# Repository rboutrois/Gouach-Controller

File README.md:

# Gouach controller

## Peripherals pinout
### Throttle
- +5V
- ADC_THROTTLE
- GND

### Torque sensor
- +5V
- PFS
- ADC_TORQUE
- CRUISE
- GND

### Brake
- +5V
- IO_BRAKE
- ADC_BRAKE
- GND

### Motor
3 Phases
- +5V
- HALL_1
- HALL_2
- HALL_3
- TEMPERATURE
- GND

### UART
- +5V
- Tx
- Rx
- GND

### UART
- CAN_H
- CAN_L

### USB
- +5V
- D+
- D-
- GND

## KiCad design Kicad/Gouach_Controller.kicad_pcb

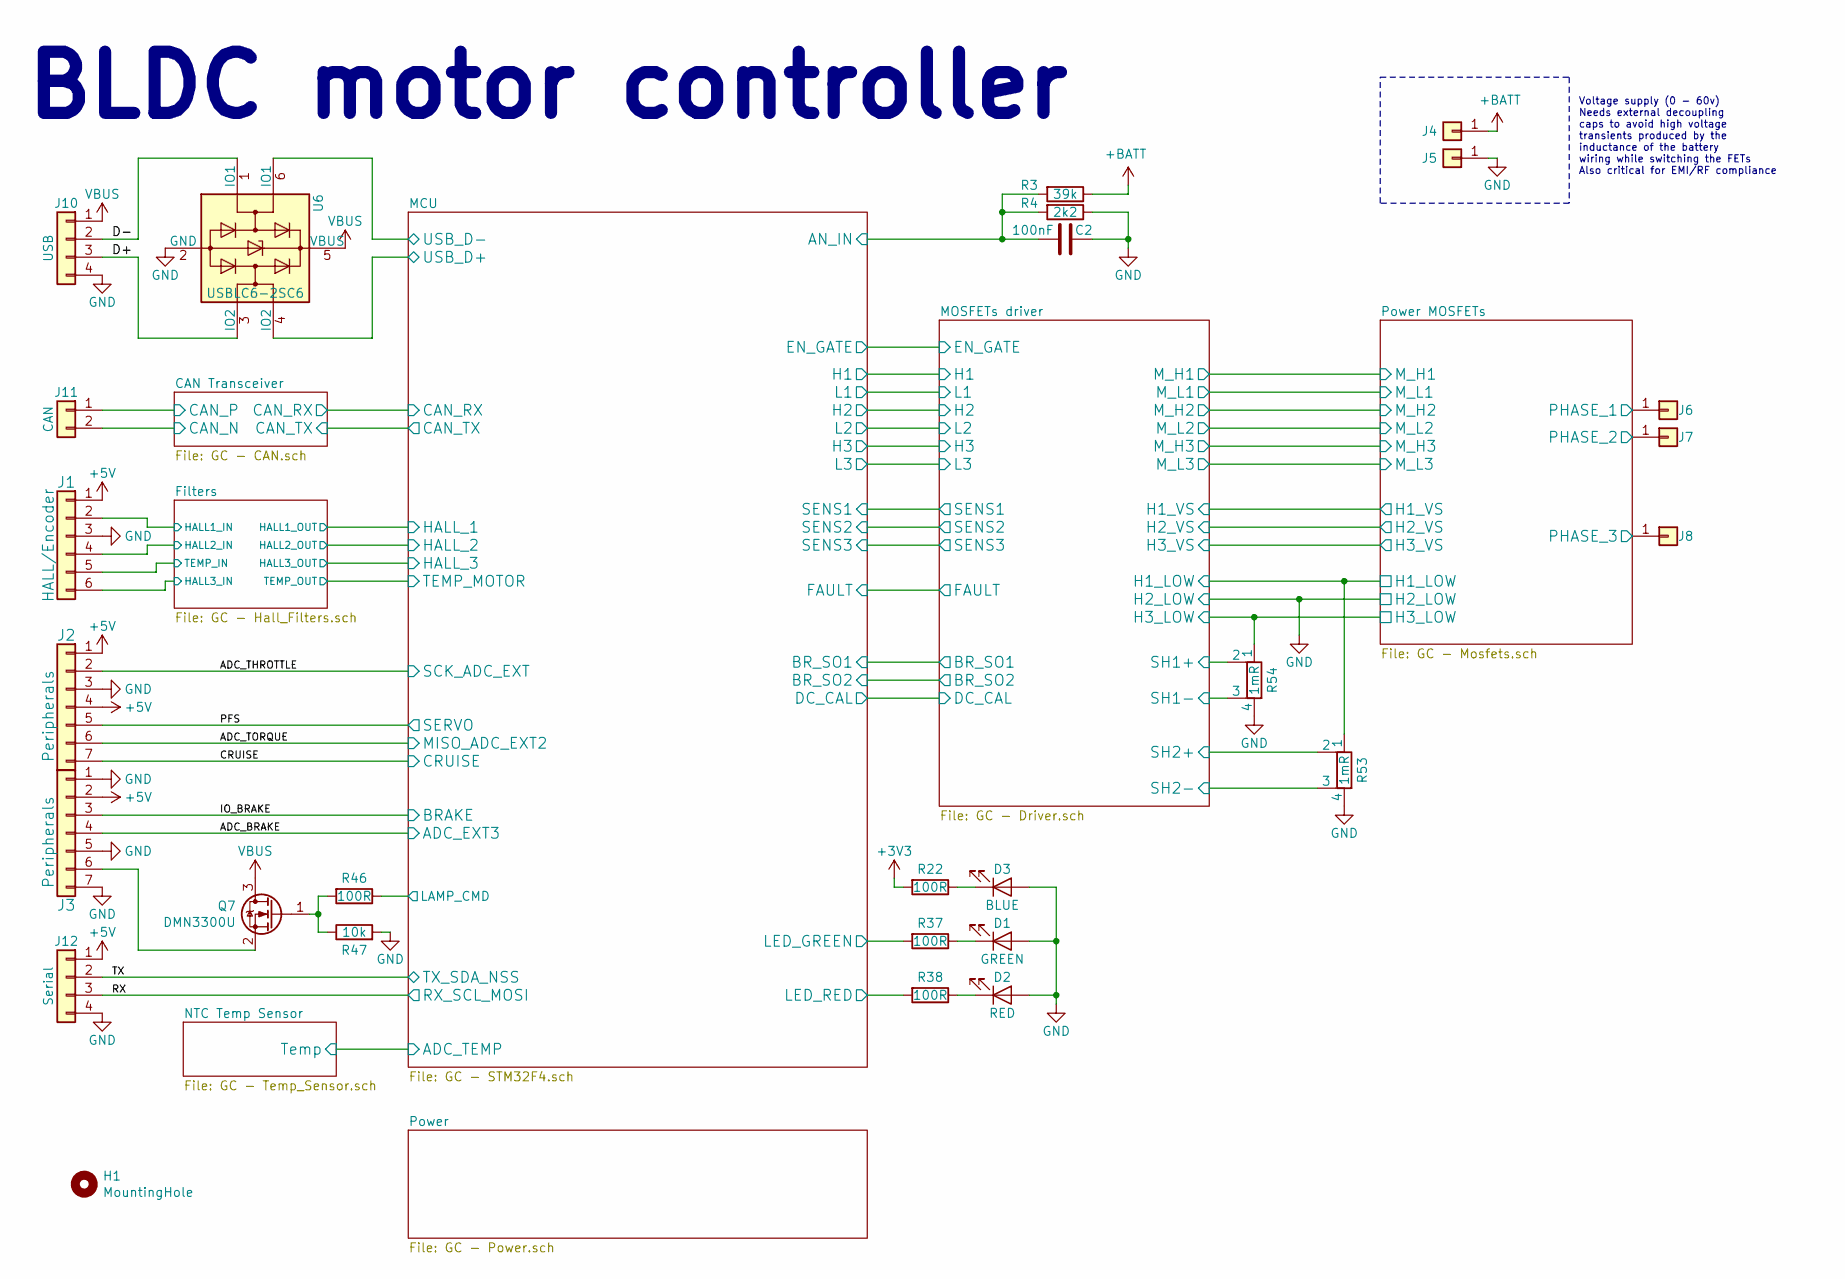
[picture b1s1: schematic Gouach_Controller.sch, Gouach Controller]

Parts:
C2: 100nF; C_0603_1608Metric
D1: GREEN; LED_0603_1608Metric
D2: RED; LED_0603_1608Metric
D3: BLUE; LED_0603_1608Metric
H1: MountingHole; MountingHole_3.2mm_M3
J1: HALL/Encoder; PinHeader_2x03_P2.54mm_Vertical
J2, J3: Peripherals; TerminalBlock_Phoenix_MPT-2.54mm_7pol
J4: BAT+; MountingHole_2.7mm_Pad_Via
J5: BAT-; MountingHole_2.7mm_Pad_Via
J6: M1; MountingHole_2.2mm_M2_Pad_Via
J7: M2; MountingHole_2.2mm_M2_Pad_Via
J8: M3; MountingHole_2.2mm_M2_Pad_Via
J10: USB; PinHeader_1x04_P2.54mm_Vertical
J11: CAN; PinHeader_1x02_P2.54mm_Vertical
J12: Serial; PinHeader_1x04_P2.54mm_Vertical
Q7: DMN3300U; SOT-23; Mouser 621-DMN3300U-7
R3: 39k; R_0603_1608Metric
R4: 2k2; R_0603_1608Metric
R22, R37, R38, R46: 100R; R_0603_1608Metric
R47: 10k; R_0603_1608Metric
R53, R54: 1mR; WSLP2726; Mouser 71-WSLP27261L000FEA
U6: USBLC6-2SC6; SOT-23-6; Mouser 511-USBLC6-2SC6

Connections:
+3V3: R22.2; also elsewhere on the board
+5V: J1.1, J2.1, J2.4, J3.2, J12.1; also elsewhere on the board
+BATT: J4.1, R3.1; also elsewhere on the board
/ADC_BRAKE: J3.4; also elsewhere on the board
/ADC_THROTTLE: J2.2; also elsewhere on the board
/ADC_TORQUE: J2.6; also elsewhere on the board
/CAN Transceiver/CAN_N: J11.2; also elsewhere on the board
/CAN Transceiver/CAN_P: J11.1; also elsewhere on the board
/CRUISE: J2.7; also elsewhere on the board
/D+: J10.3, U6.3 (IO2)
/D-: J10.2, U6.1 (IO1)
/Filters/HALL1_IN: J1.2; also elsewhere on the board
/Filters/HALL2_IN: J1.4; also elsewhere on the board
/Filters/HALL3_IN: J1.6; also elsewhere on the board
/Filters/TEMP_IN: J1.5; also elsewhere on the board
/IO_BRAKE: J3.3; also elsewhere on the board
/MCU/AN_IN: C2.2, R3.2, R4.2; also elsewhere on the board
/MCU/LAMP_CMD: R46.1; also elsewhere on the board
/MCU/LED_GREEN: R37.2; also elsewhere on the board
/MCU/LED_RED: R38.2; also elsewhere on the board
/MCU/USB_D+: U6.4 (IO2); also elsewhere on the board
/MCU/USB_D-: U6.6 (IO1); also elsewhere on the board
/MOSFETs driver/H1_LOW: R53.1; also elsewhere on the board
/MOSFETs driver/H1_VS: J6.1; also elsewhere on the board
/MOSFETs driver/H2_VS: J7.1; also elsewhere on the board
/MOSFETs driver/H3_LOW: R54.1; also elsewhere on the board
/MOSFETs driver/H3_VS: J8.1; also elsewhere on the board
/MOSFETs driver/SH1+: R54.2; also elsewhere on the board
/MOSFETs driver/SH1-: R54.3; also elsewhere on the board
/MOSFETs driver/SH2+: R53.2; also elsewhere on the board
/MOSFETs driver/SH2-: R53.3; also elsewhere on the board
/PFS: J2.5; also elsewhere on the board
/RX: J12.3; also elsewhere on the board
/TX: J12.2; also elsewhere on the board
GND: C2.1, D1.2 (A), D2.2 (A), D3.2 (A), J1.3, J2.3, J3.1, J3.5, J3.7, J5.1, J10.4, J12.4, R4.1, R47.2, R53.4, R54.4, U6.2 (GND); also elsewhere on the board
unnamed: D1.1 (K), R37.1
unnamed: D2.1 (K), R38.1
unnamed: D3.1 (K), R22.1
unnamed: J3.6, Q7.2 (S)
unnamed: Q7.1 (G), R46.2, R47.1
VBUS: J10.1, Q7.3 (D), U6.5 (VBUS); also elsewhere on the board

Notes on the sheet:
Voltage supply (0 - 60v) Needs external decoupling caps to avoid high voltage transients produced by the inductance of the battery wiring while switching the FETs Also critical for EMI/RF compliance
BLDC motor controller

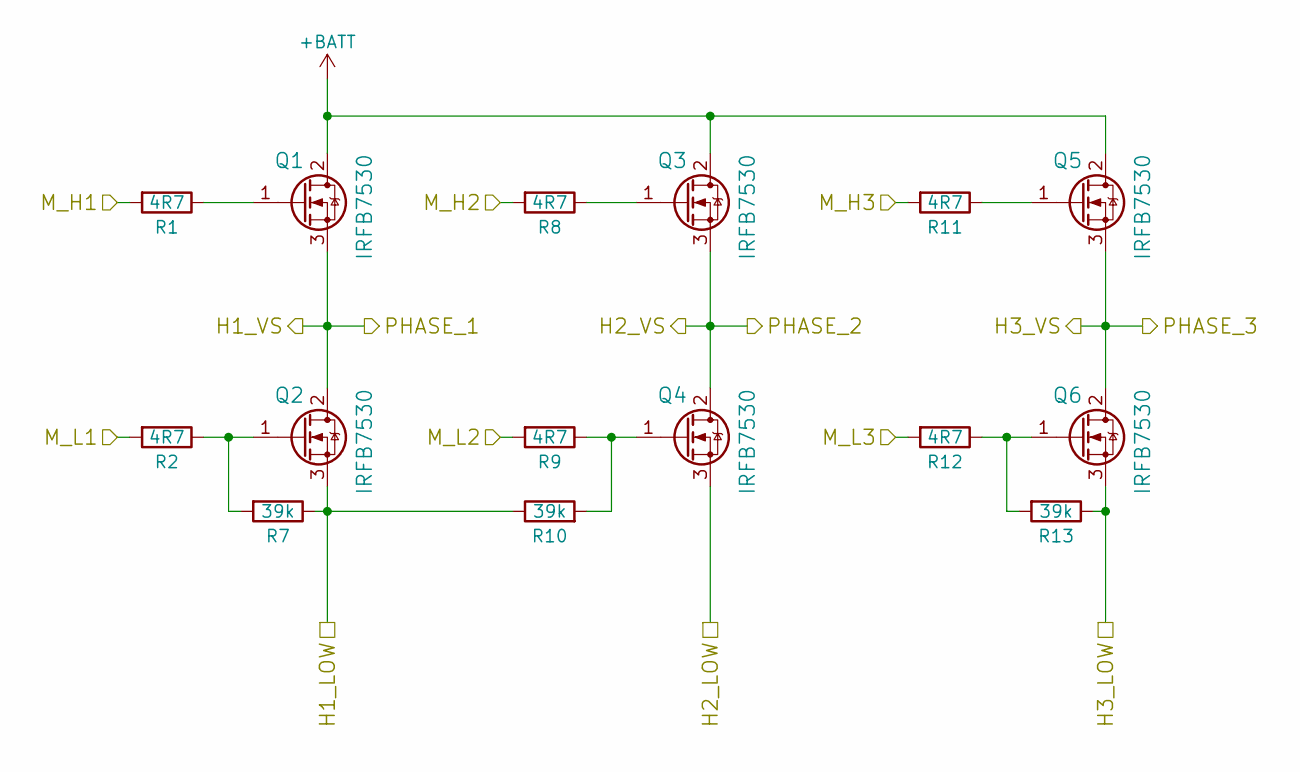
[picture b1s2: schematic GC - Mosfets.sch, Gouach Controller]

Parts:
Q1, Q2, Q3, Q4, Q5, Q6: IRFB7530; TO-220-3_Horizontal; Mouser 942-IRFB7530PBF
R1, R2, R8, R9, R11, R12: 4R7; R_0603_1608Metric
R7, R10, R13: 39k; R_0603_1608Metric

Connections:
+BATT: Q1.2 (D), Q3.2 (D), Q5.2 (D); also elsewhere on the board
/MOSFETs driver/H1_LOW: Q2.3 (S), R7.1, R10.1; also elsewhere on the board
/MOSFETs driver/H1_VS: Q1.3 (S), Q2.2 (D); also elsewhere on the board
/MOSFETs driver/H2_VS: Q3.3 (S), Q4.2 (D); also elsewhere on the board
/MOSFETs driver/H3_LOW: Q6.3 (S), R13.1; also elsewhere on the board
/MOSFETs driver/H3_VS: Q5.3 (S), Q6.2 (D); also elsewhere on the board
/MOSFETs driver/M_H1: R1.2; also elsewhere on the board
/MOSFETs driver/M_H2: R8.2; also elsewhere on the board
/MOSFETs driver/M_H3: R11.2; also elsewhere on the board
/MOSFETs driver/M_L1: R2.2; also elsewhere on the board
/MOSFETs driver/M_L2: R9.2; also elsewhere on the board
/MOSFETs driver/M_L3: R12.2; also elsewhere on the board
GND: Q4.3 (S); also elsewhere on the board
unnamed: Q1.1 (G), R1.1
unnamed: Q2.1 (G), R2.1, R7.2
unnamed: Q3.1 (G), R8.1
unnamed: Q4.1 (G), R9.1, R10.2
unnamed: Q5.1 (G), R11.1
unnamed: Q6.1 (G), R12.1, R13.2

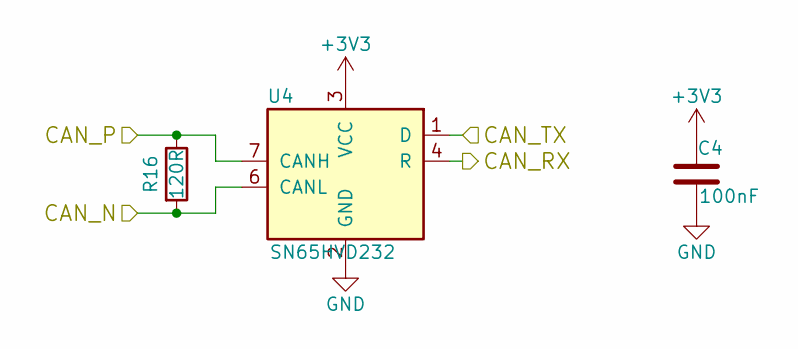
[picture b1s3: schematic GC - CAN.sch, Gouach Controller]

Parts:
C4: 100nF; C_0603_1608Metric
R16: 120R; R_0603_1608Metric
U4: SN65HVD232; SOIC-8_3.9x4.9mm_P1.27mm; Mouser 595-SN65HVD232DR

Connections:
+3V3: C4.1, U4.3 (VCC); also elsewhere on the board
/CAN Transceiver/CAN_N: R16.2, U4.6 (CANL); also elsewhere on the board
/CAN Transceiver/CAN_P: R16.1, U4.7 (CANH); also elsewhere on the board
/CAN Transceiver/CAN_RX: U4.4 (R); also elsewhere on the board
/CAN Transceiver/CAN_TX: U4.1 (D); also elsewhere on the board
GND: C4.2, U4.2 (GND); also elsewhere on the board

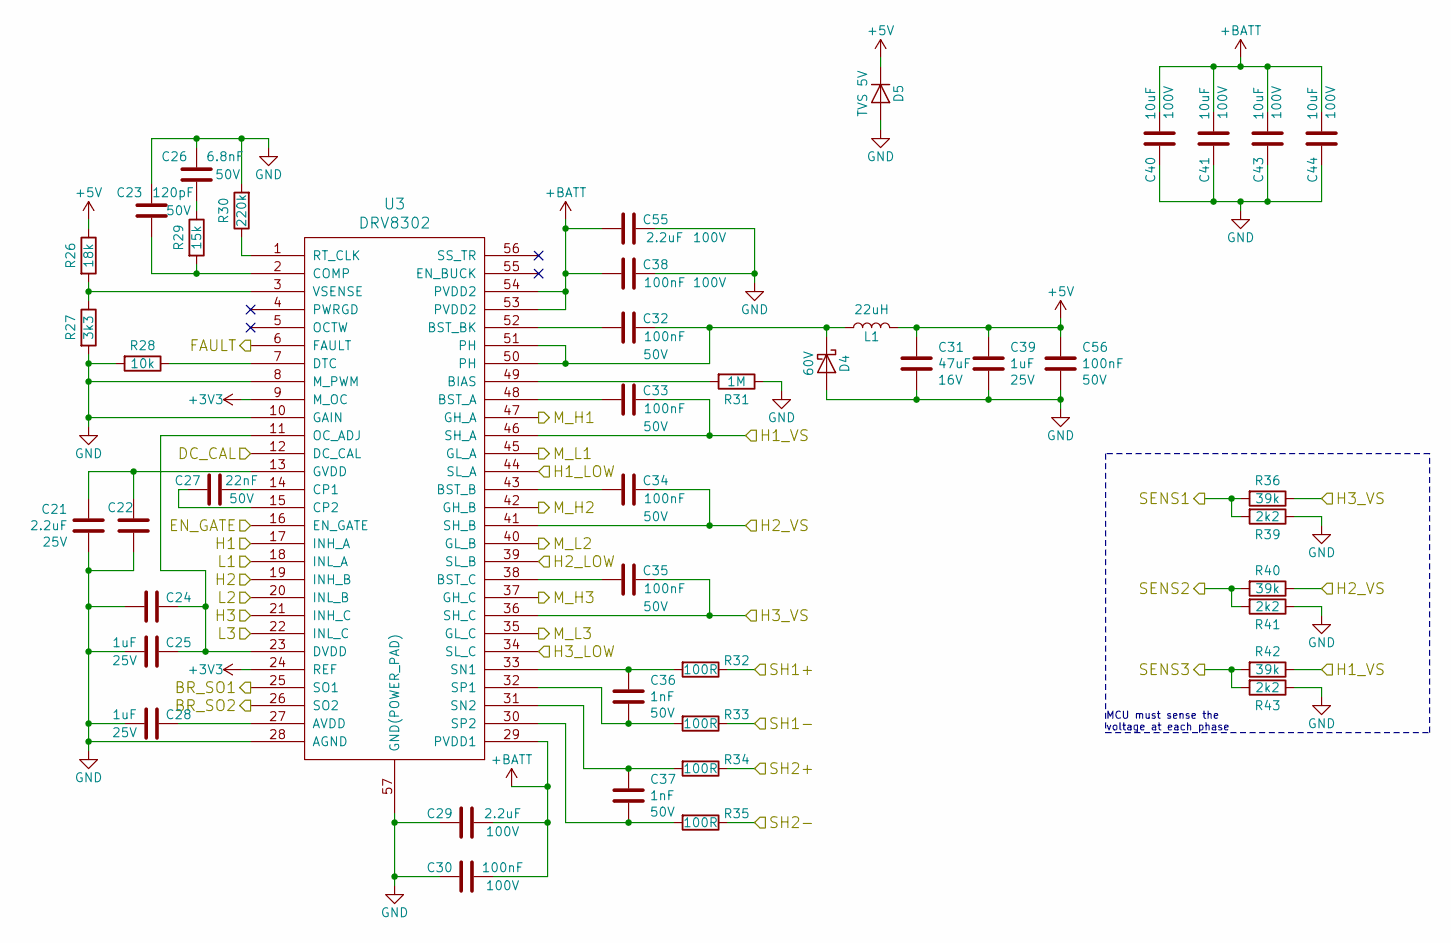
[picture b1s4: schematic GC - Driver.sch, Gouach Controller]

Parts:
C21: 2.2uF; C_0603_1608Metric
C22, C24: C_0603_1608Metric
C23: 120pF; C_0603_1608Metric
C25, C28, C39: 1uF; C_0603_1608Metric
C26: 6.8nF; C_0603_1608Metric
C27: 22nF; C_0603_1608Metric
C29, C55: 2.2uF; C_1210_3225Metric
C30, C38: 100nF; C_0805_2012Metric
C31: 47uF; C_1210_3225Metric
C32, C33, C34, C35, C56: 100nF; C_0603_1608Metric
C36, C37: 1nF; C_0603_1608Metric
C40, C41, C43, C44: 10uF; C_1206_3216Metric
D4: 60V; D_SOD-123F; Mouser 771-PMEG6020ER-115
D5: TVS 5V; D_SMA; Mouser 652-SMAJ5.0A
L1: 22uH; SDR0805; Mouser 652-SDR0805-220ML
R26: 18k; R_0603_1608Metric
R27: 3k3; R_0603_1608Metric
R28: 10k; R_0603_1608Metric
R29: 15k; R_0603_1608Metric
R30: 220k; R_0603_1608Metric
R31: 1M; R_0603_1608Metric
R32, R33, R34, R35: 100R; R_0603_1608Metric
R36, R40, R42: 39k; R_0603_1608Metric
R39, R41, R43: 2k2; R_0603_1608Metric
U3: DRV8302; Mouser 595-DRV8302DCA

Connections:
+3V3: U3.9 (M_OC), U3.24 (REF); also elsewhere on the board
+5V: C31.1, C39.1, C56.1, D5.1 (K), L1.2, R26.1; also elsewhere on the board
+BATT: C29.1, C30.1, C38.2, C40.1, C41.1, C43.1, C44.1, C55.2, U3.29 (PVDD1), U3.53 (PVDD2), U3.54 (PVDD2); also elsewhere on the board
/MCU/BR_SO1: U3.25 (SO1); also elsewhere on the board
/MCU/BR_SO2: U3.26 (SO2); also elsewhere on the board
/MCU/DC_CAL: U3.12 (DC_CAL); also elsewhere on the board
/MCU/EN_GATE: U3.16 (EN_GATE); also elsewhere on the board
/MCU/FAULT: U3.6 (FAULT); also elsewhere on the board
/MCU/H1: U3.17 (INH_A); also elsewhere on the board
/MCU/H2: U3.19 (INH_B); also elsewhere on the board
/MCU/H3: U3.21 (INH_C); also elsewhere on the board
/MCU/L1: U3.18 (INL_A); also elsewhere on the board
/MCU/L2: U3.20 (INL_B); also elsewhere on the board
/MCU/L3: U3.22 (INL_C); also elsewhere on the board
/MCU/SENS1: R36.2, R39.2; also elsewhere on the board
/MCU/SENS2: R40.2, R41.2; also elsewhere on the board
/MCU/SENS3: R42.2, R43.2; also elsewhere on the board
/MOSFETs driver/H1_LOW: U3.44 (SL_A); also elsewhere on the board
/MOSFETs driver/H1_VS: C33.1, R42.1, U3.46 (SH_A); also elsewhere on the board
/MOSFETs driver/H2_VS: C34.1, R40.1, U3.41 (SH_B); also elsewhere on the board
/MOSFETs driver/H3_LOW: U3.34 (SL_C); also elsewhere on the board
/MOSFETs driver/H3_VS: C35.1, R36.1, U3.36 (SH_C); also elsewhere on the board
/MOSFETs driver/M_H1: U3.47 (GH_A); also elsewhere on the board
/MOSFETs driver/M_H2: U3.42 (GH_B); also elsewhere on the board
/MOSFETs driver/M_H3: U3.37 (GH_C); also elsewhere on the board
/MOSFETs driver/M_L1: U3.45 (GL_A); also elsewhere on the board
/MOSFETs driver/M_L2: U3.40 (GL_B); also elsewhere on the board
/MOSFETs driver/M_L3: U3.35 (GL_C); also elsewhere on the board
/MOSFETs driver/SH1+: R32.1; also elsewhere on the board
/MOSFETs driver/SH1-: R33.1; also elsewhere on the board
/MOSFETs driver/SH2+: R34.1; also elsewhere on the board
/MOSFETs driver/SH2-: R35.1; also elsewhere on the board
GND: C21.2, C22.2, C23.1, C24.1, C25.1, C26.1, C28.1, C29.2, C30.2, C31.2, C38.1, C39.2, C40.2, C41.2, C43.2, C44.2, C55.1, C56.2, D4.2 (A), D5.2 (A), R27.2, R28.2, R30.2, R31.1, R39.1, R41.1, R43.1, U3.8 (M_PWM), U3.10 (GAIN), U3.28 (AGND), U3.39 (SL_B), U3.57 (GND(POWER_PAD)); also elsewhere on the board
unnamed: C21.1, C22.1, U3.13 (GVDD)
unnamed: C23.2, R29.2, U3.2 (COMP)
unnamed: C24.2, C25.2, U3.11 (OC_ADJ), U3.23 (DVDD)
unnamed: C26.2, R29.1
unnamed: C27.1, U3.14 (CP1)
unnamed: C27.2, U3.15 (CP2)
unnamed: C28.2, U3.27 (AVDD)
unnamed: C32.1, D4.1 (K), L1.1, U3.50 (PH), U3.51 (PH)
unnamed: C32.2, U3.52 (BST_BK)
unnamed: C33.2, U3.48 (BST_A)
unnamed: C34.2, U3.43 (BST_B)
unnamed: C35.2, U3.38 (BST_C)
unnamed: C36.1, R32.2, U3.33 (SN1)
unnamed: C36.2, R33.2, U3.32 (SP1)
unnamed: C37.1, R34.2, U3.31 (SN2)
unnamed: C37.2, R35.2, U3.30 (SP2)
unnamed: R26.2, R27.1, U3.3 (VSENSE)
unnamed: R28.1, U3.7 (DTC)
unnamed: R30.1, U3.1 (RT_CLK)
unnamed: R31.2, U3.49 (BIAS)

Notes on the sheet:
MCU must sense the voltage at each phase

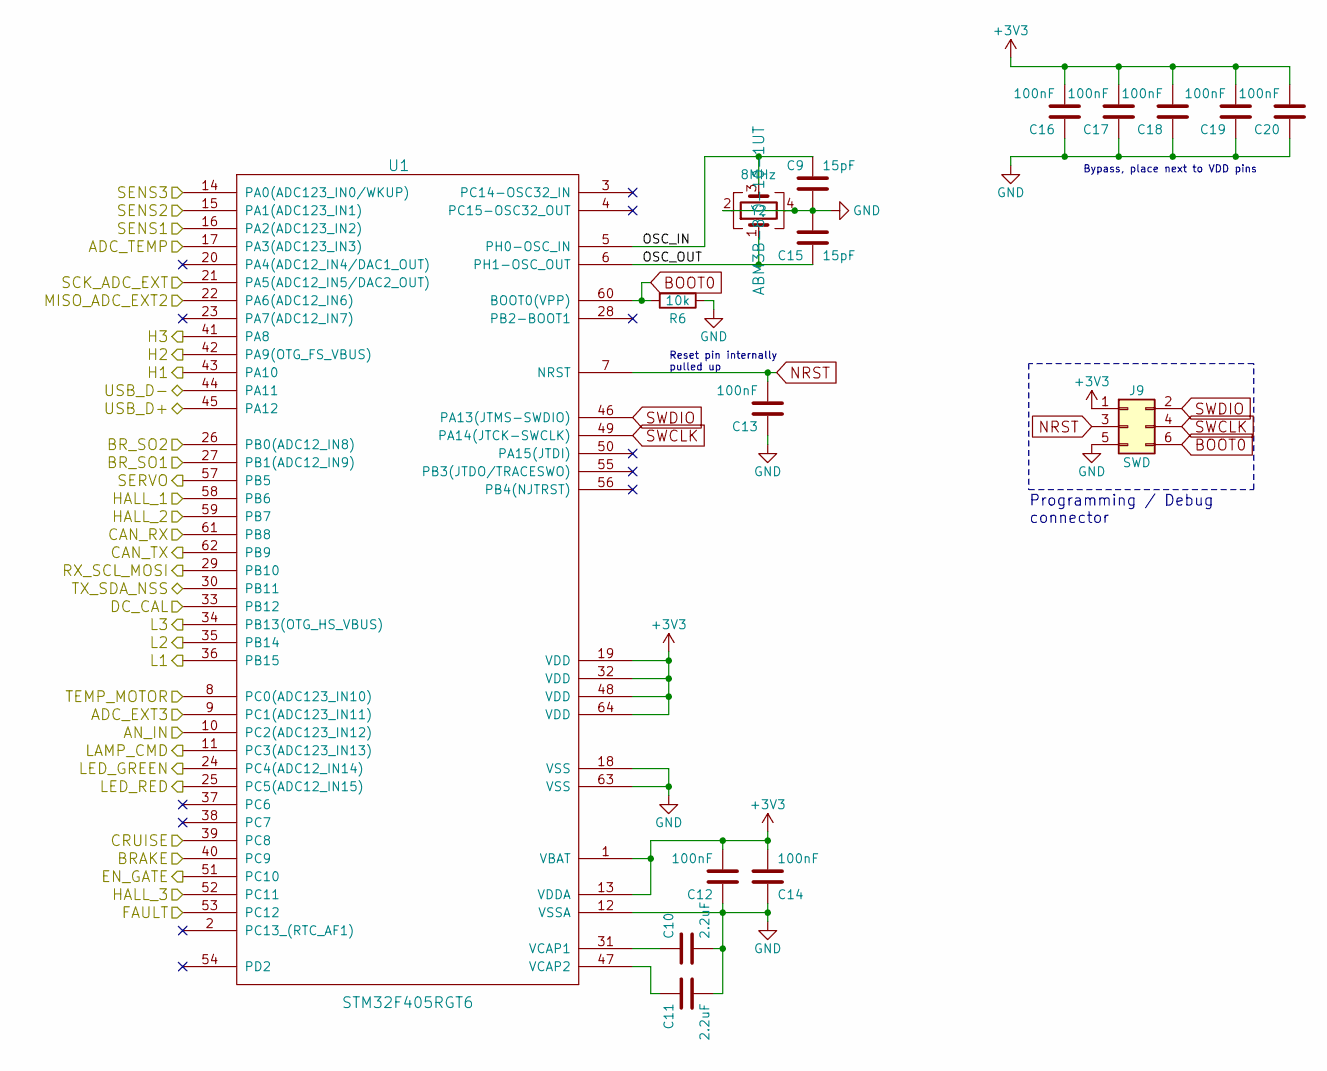
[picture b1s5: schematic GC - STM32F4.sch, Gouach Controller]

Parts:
C9, C15: 15pF; C_0603_1608Metric
C10, C11: 2.2uF; C_0603_1608Metric
C12, C13, C14, C16, C17, C18, C19, C20: 100nF; C_0603_1608Metric
J9: SWD; Tag-Connect_TC2030-IDC-NL_2x03_P1.27mm_Vertical
R6: 10k; R_0603_1608Metric
U1: STM32F405RGT6; LQFP-64_10x10mm_P0.5mm; Mouser 511-STM32F405RGT6
Y2: 8MHz; Crystal_SMD_5032-4Pin_5.0x3.2mm; Mouser 815-ABM3B-8.0-10-1UT

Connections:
+3V3: C12.2, C14.2, C16.2, C17.2, C18.2, C19.2, C20.2, J9.1, U1.1 (VBAT), U1.13 (VDDA), U1.19 (VDD), U1.32 (VDD), U1.48 (VDD), U1.64 (VDD); also elsewhere on the board
/ADC_BRAKE: U1.9 (PC1(ADC123_IN11)); also elsewhere on the board
/ADC_THROTTLE: U1.21 (PA5(ADC12_IN5/DAC2_OUT)); also elsewhere on the board
/ADC_TORQUE: U1.22 (PA6(ADC12_IN6)); also elsewhere on the board
/CAN Transceiver/CAN_RX: U1.61 (PB8); also elsewhere on the board
/CAN Transceiver/CAN_TX: U1.62 (PB9); also elsewhere on the board
/CRUISE: U1.39 (PC8); also elsewhere on the board
/Filters/HALL1_OUT: U1.58 (PB6); also elsewhere on the board
/Filters/HALL2_OUT: U1.59 (PB7); also elsewhere on the board
/Filters/HALL3_OUT: U1.52 (PC11); also elsewhere on the board
/Filters/TEMP_IN: U1.8 (PC0(ADC123_IN10)); also elsewhere on the board
/IO_BRAKE: U1.40 (PC9); also elsewhere on the board
/MCU/ADC_TEMP: U1.17 (PA3(ADC123_IN3)); also elsewhere on the board
/MCU/AN_IN: U1.10 (PC2(ADC123_IN12)); also elsewhere on the board
/MCU/BR_SO1: U1.27 (PB1(ADC12_IN9)); also elsewhere on the board
/MCU/BR_SO2: U1.26 (PB0(ADC12_IN8)); also elsewhere on the board
/MCU/DC_CAL: U1.33 (PB12); also elsewhere on the board
/MCU/EN_GATE: U1.51 (PC10); also elsewhere on the board
/MCU/FAULT: U1.53 (PC12); also elsewhere on the board
/MCU/H1: U1.43 (PA10); also elsewhere on the board
/MCU/H2: U1.42 (PA9(OTG_FS_VBUS)); also elsewhere on the board
/MCU/H3: U1.41 (PA8); also elsewhere on the board
/MCU/L1: U1.36 (PB15); also elsewhere on the board
/MCU/L2: U1.35 (PB14); also elsewhere on the board
/MCU/L3: U1.34 (PB13(OTG_HS_VBUS)); also elsewhere on the board
/MCU/LAMP_CMD: U1.11 (PC3(ADC123_IN13)); also elsewhere on the board
/MCU/LED_GREEN: U1.24 (PC4(ADC12_IN14)); also elsewhere on the board
/MCU/LED_RED: U1.25 (PC5(ADC12_IN15)); also elsewhere on the board
/MCU/OSC_IN: C9.1, U1.5 (PH0-OSC_IN), Y2.3
/MCU/OSC_OUT: C15.2, U1.6 (PH1-OSC_OUT), Y2.1
/MCU/SENS1: U1.16 (PA2(ADC123_IN2)); also elsewhere on the board
/MCU/SENS2: U1.15 (PA1(ADC123_IN1)); also elsewhere on the board
/MCU/SENS3: U1.14 (PA0(ADC123_IN0/WKUP)); also elsewhere on the board
/MCU/USB_D+: U1.45 (PA12); also elsewhere on the board
/MCU/USB_D-: U1.44 (PA11); also elsewhere on the board
/PFS: U1.57 (PB5); also elsewhere on the board
/RX: U1.29 (PB10); also elsewhere on the board
/TX: U1.30 (PB11); also elsewhere on the board
BOOT0: J9.6, R6.2, U1.60 (BOOT0(VPP))
GND: C9.2, C10.2, C11.2, C12.1, C13.1, C14.1, C15.1, C16.1, C17.1, C18.1, C19.1, C20.1, J9.5, R6.1, U1.12 (VSSA), U1.18 (VSS), U1.63 (VSS), Y2.2, Y2.4; also elsewhere on the board
NRST: C13.2, J9.3, U1.7 (NRST)
unnamed: C10.1, U1.31 (VCAP1)
unnamed: C11.1, U1.47 (VCAP2)
SWCLK: J9.4, U1.49 (PA14(JTCK-SWCLK))
SWDIO: J9.2, U1.46 (PA13(JTMS-SWDIO))

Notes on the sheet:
Programming / Debug connector
Reset pin internally pulled up
Bypass, place next to VDD pins

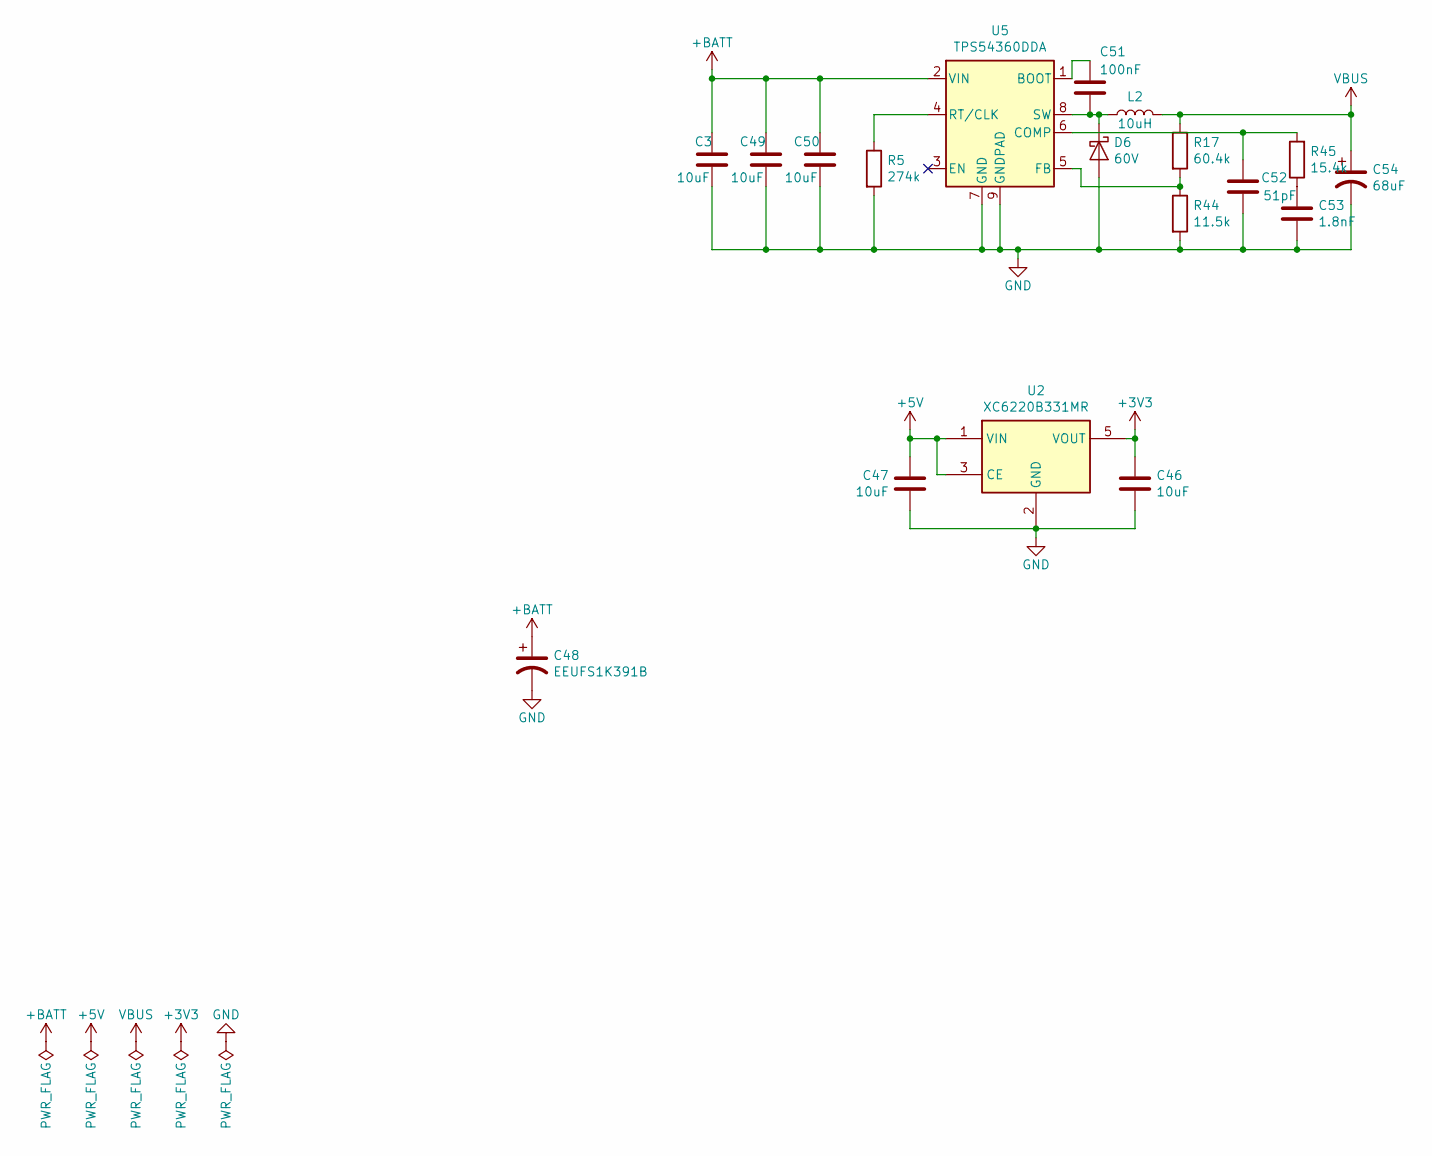
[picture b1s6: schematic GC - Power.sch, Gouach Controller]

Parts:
C3, C49, C50: 10uF; C_1206_3216Metric
C46, C47: 10uF; C_0603_1608Metric
C48: EEUFS1K391B; Capacitor_Horizontal
C51: 100nF; C_0603_1608Metric
C52: 51pF; C_0603_1608Metric
C53: 1.8nF; C_0603_1608Metric
C54: 68uF; C_Elec_5x5.8
D6: 60V; D_SOD-123F; Mouser 771-PMEG6020ER-115
L2: 10uH; L_Coilcraft_XAL5030; Mouser 994-XAL5050-103MEB
R5: 274k; R_0603_1608Metric
R17: 60.4k; R_0603_1608Metric
R44: 11.5k; R_0603_1608Metric
R45: 15.4k; R_0603_1608Metric
U2: XC6220B331MR; SOT-23-5; Mouser 865-XC6220B331MR-G
U5: TPS54360DDA; TI_SO-PowerPAD-8; Mouser 595-TPS54360DDA

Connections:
+3V3: C46.1, U2.5 (VOUT); also elsewhere on the board
+5V: C47.1, U2.1 (VIN), U2.3 (CE); also elsewhere on the board
+BATT: C3.1, C48.1, C49.1, C50.1, U5.2 (VIN); also elsewhere on the board
GND: C3.2, C46.2, C47.2, C48.2, C49.2, C50.2, C52.2, C53.2, C54.2, D6.2 (A), R5.2, R44.2, U2.2 (GND), U5.7 (GND), U5.9 (GNDPAD); also elsewhere on the board
unnamed: C51.1, U5.1 (BOOT)
unnamed: C51.2, D6.1 (K), L2.1, U5.8 (SW)
unnamed: C52.1, R45.2, U5.6 (COMP)
unnamed: C53.1, R45.1
unnamed: R5.1, U5.4 (RT/CLK)
unnamed: R17.2, R44.1, U5.5 (FB)
VBUS: C54.1, L2.2, R17.1; also elsewhere on the board

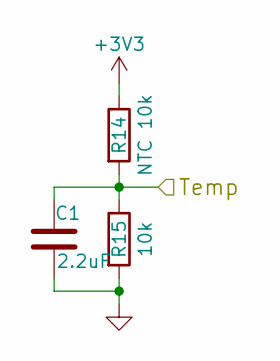
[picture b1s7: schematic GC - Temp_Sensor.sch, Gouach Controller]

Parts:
C1: 2.2uF; C_0603_1608Metric
R14: NTC 10k; R_0603_1608Metric
R15: 10k; R_0603_1608Metric

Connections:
+3V3: R14.1; also elsewhere on the board
/MCU/ADC_TEMP: C1.1, R14.2, R15.1; also elsewhere on the board
GND: C1.2, R15.2; also elsewhere on the board

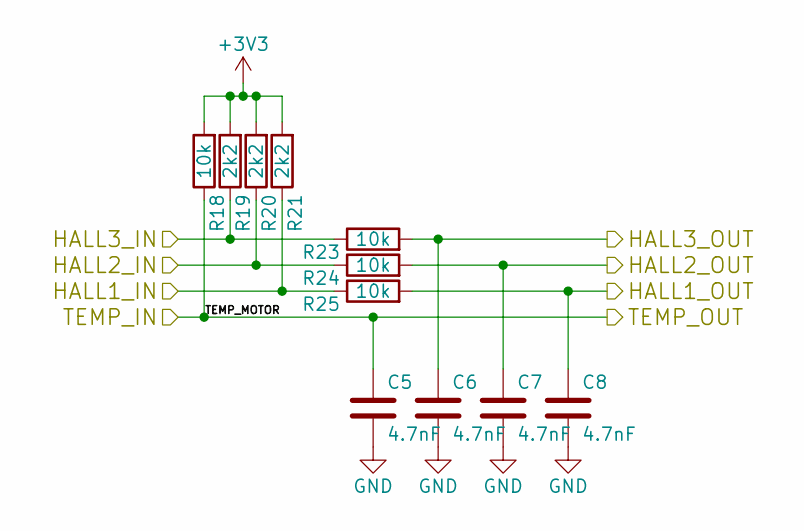
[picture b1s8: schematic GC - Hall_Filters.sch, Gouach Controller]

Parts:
C5, C6, C7, C8: 4.7nF; C_0603_1608Metric
R18, R23, R24, R25: 10k; R_0603_1608Metric
R19, R20, R21: 2k2; R_0603_1608Metric

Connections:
+3V3: R18.2, R19.2, R20.2, R21.2; also elsewhere on the board
/Filters/HALL1_IN: R21.1, R25.1; also elsewhere on the board
/Filters/HALL1_OUT: C8.1, R25.2; also elsewhere on the board
/Filters/HALL2_IN: R20.1, R24.1; also elsewhere on the board
/Filters/HALL2_OUT: C7.1, R24.2; also elsewhere on the board
/Filters/HALL3_IN: R19.1, R23.1; also elsewhere on the board
/Filters/HALL3_OUT: C6.1, R23.2; also elsewhere on the board
/Filters/TEMP_IN: C5.1, R18.1; also elsewhere on the board
GND: C5.2, C6.2, C7.2, C8.2; also elsewhere on the board

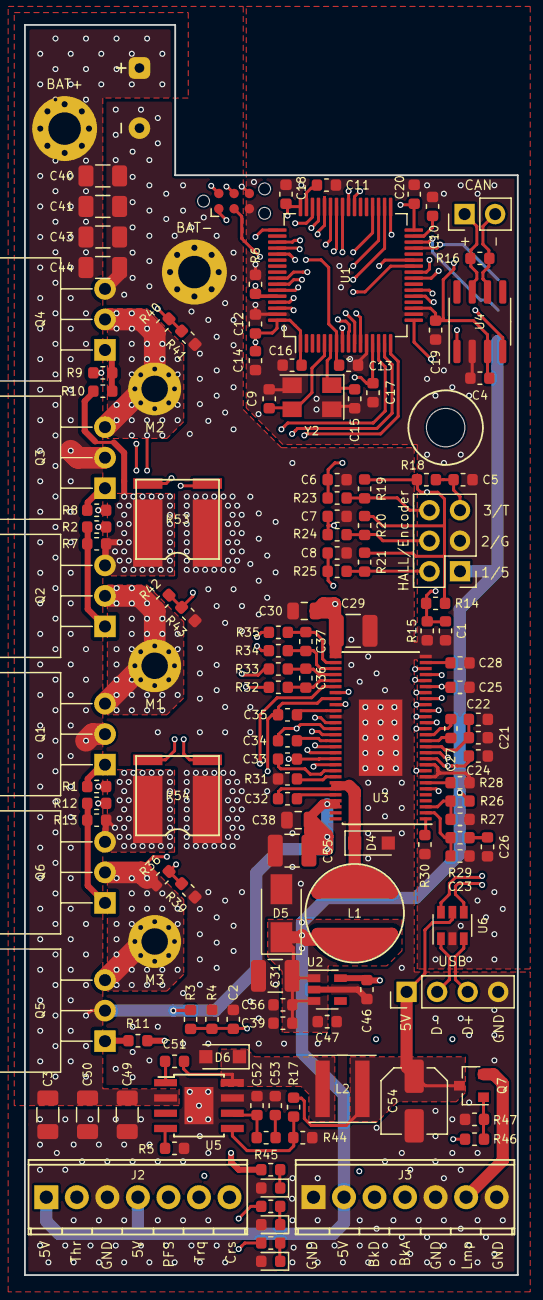
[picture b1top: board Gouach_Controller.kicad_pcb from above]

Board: 4 copper layers, 41.0 x 104.0 mm, 138 parts (1 on the bottom side), 107 nets.

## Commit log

2020-02-18 Components Placement
2020-02-20 Passives changed from 0805 to 0603
2020-02-22 Components placed
2020-03-03 Modified datasheet reference
2020-03-03 Adjusting capacitor size/value
2020-03-03 Remove .ioc files
2020-03-03 Routing done
2020-03-03 Adjusted cap size/value + add ESD protection on USB
2020-03-09 Add Gouach-Controller libraries
2020-03-09 Fixed libraries issues
2020-03-09 Add Mouser order number
2020-04-01 Add capacitor ref
2020-04-01 Change R22 value
2020-04-01 Add HTML BOM
